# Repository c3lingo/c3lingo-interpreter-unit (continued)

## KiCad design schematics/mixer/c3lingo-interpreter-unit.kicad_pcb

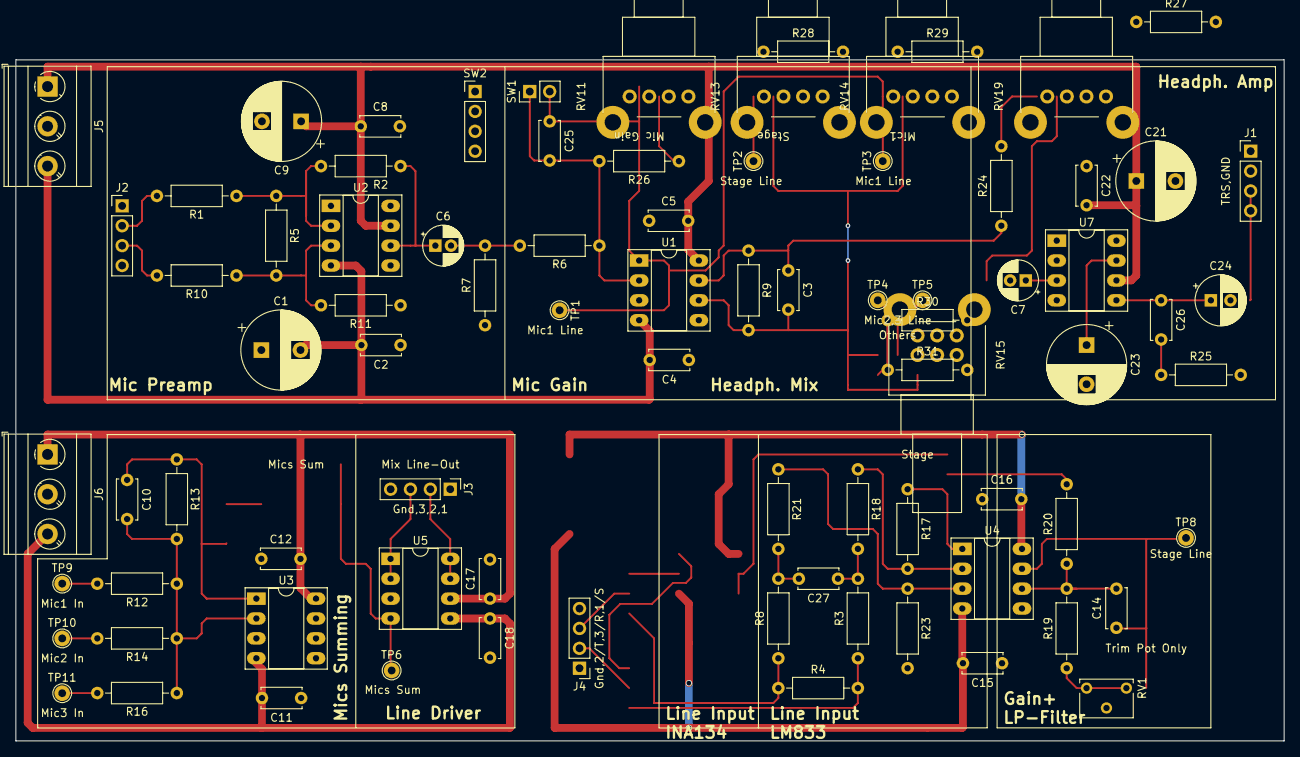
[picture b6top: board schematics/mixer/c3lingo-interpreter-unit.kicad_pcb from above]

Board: 2 copper layers, 162.0 x 87.0 mm, 83 parts (0 on the bottom side), 43 nets.

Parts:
C1, C9, C21, C23: 100uF; CP_Radial_D10.0mm_P5.00mm
C2, C4, C5, C8, C11, C12, C15, C16, C22, C25: 100nF; C_Disc_D5.0mm_W2.5mm_P5.00mm
C3, C10: 22pF; C_Disc_D5.0mm_W2.5mm_P5.00mm
C6, C7: 1uF; CP_Radial_D5.0mm_P2.00mm
C14: 47pF; C_Disc_D5.0mm_W2.5mm_P5.00mm
C17, C18: 1uF; C_Disc_D5.0mm_W2.5mm_P5.00mm
C24: 220uF; CP_Radial_D6.3mm_P2.50mm
C26: 47nF; C_Disc_D5.0mm_W2.5mm_P5.00mm
C27: 220pF; C_Disc_D5.0mm_W2.5mm_P5.00mm
J1: Headphone 1; PinHeader_1x04_P2.54mm_Vertical
J2: Mic 1; PinHeader_1x04_P2.54mm_Vertical
J3: Mix Line-Out; PinHeader_1x04_P2.54mm_Vertical
J4: Stage Line-In; PinHeader_1x04_P2.54mm_Vertical
J5, J6: PowerSupply; TerminalBlock_MetzConnect_Type073_RT02603HBLU_1x03_P5.08mm_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
R1, R10: 1K 1%; R_Axial_DIN0207_L6.3mm_D2.5mm_P10.16mm_Horizontal
R2, R11: 330K 1%; R_Axial_DIN0207_L6.3mm_D2.5mm_P10.16mm_Horizontal
R3, R8, R17, R18, R21, R23: 10K; R_Axial_DIN0207_L6.3mm_D2.5mm_P10.16mm_Horizontal
R4: 3.3K; R_Axial_DIN0207_L6.3mm_D2.5mm_P10.16mm_Horizontal
R5: 27K 1%; R_Axial_DIN0207_L6.3mm_D2.5mm_P10.16mm_Horizontal
R6: 1.5K; R_Axial_DIN0207_L6.3mm_D2.5mm_P10.16mm_Horizontal
R7: 470R; R_Axial_DIN0207_L6.3mm_D2.5mm_P10.16mm_Horizontal
R9, R12, R13, R14, R16, R19, R28, R29, R30, R31: 22K; R_Axial_DIN0207_L6.3mm_D2.5mm_P10.16mm_Horizontal
R20: 47K; R_Axial_DIN0207_L6.3mm_D2.5mm_P10.16mm_Horizontal
R24: 330K; R_Axial_DIN0207_L6.3mm_D2.5mm_P10.16mm_Horizontal
R25: 12R; R_Axial_DIN0207_L6.3mm_D2.5mm_P10.16mm_Horizontal
R26: 270R; R_Axial_DIN0207_L6.3mm_D2.5mm_P10.16mm_Horizontal
R27: 2.2K; R_Axial_DIN0207_L6.3mm_D2.5mm_P10.16mm_Horizontal
RV1: 100K; Potentiometer_Vishay_T73XX_Horizontal
RV11, RV13, RV14, RV19: 50K log.; Potentiometer_Alps_RK11K_Single_Horizontal
RV15: 50K log. st.; Potentiometer_Alps_RK09L_Double_Horizontal
SW1: Mute_1; PinHeader_1x02_P2.54mm_Vertical
SW2: OnAir_1; PinHeader_1x04_P2.54mm_Vertical
TP1, TP3, TP9: Mic1; TestPoint_THTPad_D2.0mm_Drill1.0mm
TP2, TP8: Stage; TestPoint_THTPad_D2.0mm_Drill1.0mm
TP4, TP10: Mic2; TestPoint_THTPad_D2.0mm_Drill1.0mm
TP5, TP11: Mic3; TestPoint_THTPad_D2.0mm_Drill1.0mm
TP6: MicSum; TestPoint_THTPad_D2.0mm_Drill1.0mm
U1, U3, U4: LM833N; DIP-8_W7.62mm_Socket_LongPads
U2: NE5534; DIP-8_W7.62mm_Socket_LongPads
U5: DRV134PA; DIP-8_W7.62mm_Socket_LongPads
U7: LM386N-4; DIP-8_W7.62mm_Socket_LongPads

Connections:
+15V: C5.2, C8.1, C9.1, C12.2, C16.2, C17.1, C21.1, C22.2, J5.1, J6.1, U1.8, U2.7, U3.8, U4.8, U5.6, U7.6
-15V: C1.2, C2.2, C4.2, C11.2, C15.2, C18.1, J5.3, J6.3, U1.4, U2.4, U3.4, U4.4, U5.5
GNDREF: C1.1, C2.1, C4.1, C5.1, C8.2, C9.2, C11.1, C12.1, C15.1, C16.1, C17.2, C18.2, C21.2, C22.1, C23.2, J2.1, J3.1, J4.1, J5.2, J6.2, R7.1, R11.1, R23.2, R25.2, R27.2, RV13.1, RV14.1, RV15.1, RV15.4, U1.3, U1.5, U3.3, U4.5, U5.3, U7.2, U7.4
Mic1: C25.1, R12.2, RV11.2, RV14.3, SW1.2, TP1.1, TP3.1, TP9.1, U1.1
unnamed: C3.1, R9.1, R24.1, U1.7
unnamed: C3.2, R9.2, R28.1, R29.1, R30.1, R31.1, U1.6
unnamed: C6.1, R2.1, U2.6
unnamed: C6.2, R6.2, R7.2
unnamed: C7.1, RV19.2
unnamed: C7.2, U7.3
unnamed: C10.1, R13.1, TP6.1, U3.1, U5.4
unnamed: C10.2, R12.1, R13.2, R14.1, R16.1, U3.2
unnamed: C14.2, R19.2, R20.1, U4.6
unnamed: C23.1, U7.7
unnamed: C24.1, C26.1, U7.5
unnamed: C25.2, R6.1, R26.2, SW1.1, U1.2
unnamed: C26.2, R25.1
unnamed: C27.1, R3.2, R18.2
unnamed: C27.2, R8.2, R21.2
unnamed: J2.2, R1.2
unnamed: J2.3, R10.2
unnamed: J3.2, U5.7, U5.8
unnamed: J3.3, U5.1, U5.2
unnamed: J4.2, R3.1, R4.2
unnamed: J4.3, R4.1, R8.1
unnamed: R1.1, R2.2, R5.1, U2.2
unnamed: R5.2, R10.1, R11.2, U2.3
unnamed: R14.2, TP10.1
unnamed: R16.2, TP11.1
unnamed: R17.1, R20.2, U4.1
unnamed: R17.2, R18.1, U4.2
unnamed: R19.1, RV1.1
unnamed: R21.1, R23.1, U4.3
unnamed: R24.2, RV19.3
unnamed: R26.1, RV11.1
unnamed: R27.1, RV19.1
unnamed: R28.2, RV13.2
unnamed: R29.2, RV14.2
unnamed: R30.2, RV15.5
unnamed: R31.2, RV15.2
unnamed: RV15.3, TP5.1
unnamed: RV15.6, TP4.1
Stage: C14.1, RV1.2, RV13.3, TP2.1, TP8.1, U4.7

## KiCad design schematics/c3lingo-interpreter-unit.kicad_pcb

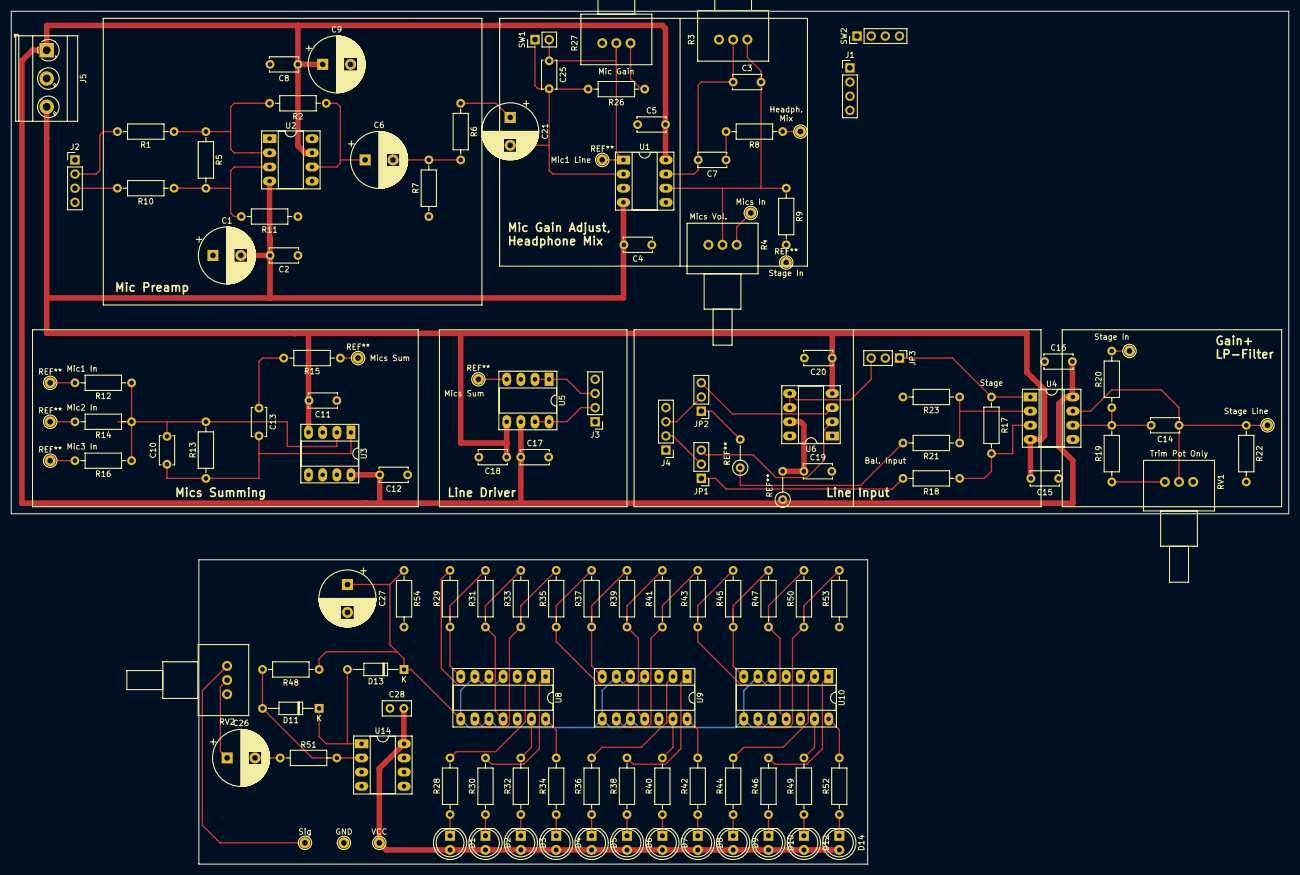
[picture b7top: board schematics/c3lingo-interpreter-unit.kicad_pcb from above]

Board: 2 copper layers, 229.2 x 153.0 mm, 117 parts (0 on the bottom side), 77 nets.

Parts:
C1, C9: 100uF; CP_Radial_D10.0mm_P5.00mm
C2, C4, C5, C8, C11, C12, C15, C16: 100nF; C_Disc_D5.0mm_W2.5mm_P5.00mm
C3, C10: 22pF; C_Disc_D5.0mm_W2.5mm_P5.00mm
C6, C21: 10uF; CP_Radial_D10.0mm_P5.00mm
C7: 10nF; C_Disc_D5.0mm_W2.5mm_P5.00mm
C13: 4.7pF; C_Disc_D5.0mm_W2.5mm_P5.00mm
C14: 47pF; C_Disc_D5.0mm_W2.5mm_P5.00mm
C17, C18, C19, C20: 1uF; C_Disc_D5.0mm_W2.5mm_P5.00mm
C25: 0.1uF; C_Disc_D5.0mm_W2.5mm_P5.00mm
C26: TODO; CP_Radial_D10.0mm_P5.00mm
C27: 2.2uF; CP_Radial_D10.0mm_P5.00mm
C28: 100nF; C_Disc_D5.0mm_W2.5mm_P2.50mm
D1, D9, D10, D12, D14: LED rd; LED_D5.0mm
D2, D3, D7, D8: LED ye; LED_D5.0mm
D4, D5, D6: LED gn; LED_D5.0mm
D11, D13: 1N4148; D_DO-35_SOD27_P10.16mm_Horizontal
GND: TestPoint_THTPad_D2.0mm_Drill1.0mm
J1: Headphone 1; PinHeader_1x04_P2.54mm_Vertical
J2: Mic 1; PinHeader_1x04_P2.54mm_Vertical
J3: Mix Line-Out; PinHeader_1x04_P2.54mm_Vertical
J4: Stage Line-In; PinHeader_1x04_P2.54mm_Vertical
J5: PowerSupply; TerminalBlock_MetzConnect_Type073_RT02603HBLU_1x03_P5.08mm_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
JP1: Stage Hot; PinHeader_1x03_P2.54mm_Vertical
JP2: Stage Cold; PinHeader_1x03_P2.54mm_Vertical
JP3: Stage Out; PinHeader_1x03_P2.54mm_Vertical
Mics In: TestPoint_THTPad_D2.0mm_Drill1.0mm
R1, R10: 1K 1%; R_Axial_DIN0207_L6.3mm_D2.5mm_P10.16mm_Horizontal
R2, R11: 330K 1%; R_Axial_DIN0207_L6.3mm_D2.5mm_P10.16mm_Horizontal
R3, R4: 22K; Potentiometer_Vishay_148-149_Single_Horizontal
R5: 27K 1%; R_Axial_DIN0207_L6.3mm_D2.5mm_P10.16mm_Horizontal
R6, R26: 120R; R_Axial_DIN0207_L6.3mm_D2.5mm_P10.16mm_Horizontal
R7: 5.6K; R_Axial_DIN0207_L6.3mm_D2.5mm_P10.16mm_Horizontal
R8, R15: 47R; R_Axial_DIN0207_L6.3mm_D2.5mm_P10.16mm_Horizontal
R9, R12, R13, R14, R16, R19, R22: 22K; R_Axial_DIN0207_L6.3mm_D2.5mm_P10.16mm_Horizontal
R17, R18, R21, R23, R28, R29, R30, R31, R32, R33, R34, R35, R36, R37, R38, R39, R40, R41, R42, R43, R44, R45, R46, R47, R49, R50, R52: R; R_Axial_DIN0207_L6.3mm_D2.5mm_P10.16mm_Horizontal
R20: 47K; R_Axial_DIN0207_L6.3mm_D2.5mm_P10.16mm_Horizontal
R27: 25K; Potentiometer_Vishay_148-149_Single_Horizontal
R48: 100K; R_Axial_DIN0207_L6.3mm_D2.5mm_P10.16mm_Horizontal
R51: 25K; R_Axial_DIN0207_L6.3mm_D2.5mm_P10.16mm_Horizontal
R53: 1K; R_Axial_DIN0207_L6.3mm_D2.5mm_P10.16mm_Horizontal
R54: 10K; R_Axial_DIN0207_L6.3mm_D2.5mm_P10.16mm_Horizontal
RV1: 100K; Potentiometer_Vishay_148-149_Single_Horizontal
RV2: 50K; Potentiometer_Vishay_148-149_Single_Horizontal
SW1: Mute_1; PinHeader_1x02_P2.54mm_Vertical
SW2: OnAir_1; PinHeader_1x04_P2.54mm_Vertical
Sig: TestPoint_THTPad_D2.0mm_Drill1.0mm
U1, U3, U4, U14: LM833N; DIP-8_W7.62mm_Socket_LongPads
U2: NE5534; DIP-8_W7.62mm_Socket_LongPads
U5: DRV134PA; DIP-8_W7.62mm_Socket_LongPads
U6: INA134PA; DIP-8_W7.62mm_Socket_LongPads
U8, U9, U10: LM339; DIP-14_W7.62mm_Socket_LongPads
VCC: TestPoint_THTPad_D2.0mm_Drill1.0mm

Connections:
+15V: C5.2, C8.1, C9.1, C12.2, C16.2, C17.1, C19.1, C28.2, D1.2, D2.2, D3.2, D4.2, D5.2, D6.2, D7.2, D8.2, D9.2, D10.2, D12.2, D14.2, J5.1, U1.8, U2.7, U3.8, U4.8, U5.6, U6.7, U8.3, U9.3, U10.3, U14.8, VCC.1
-15V: C1.2, C2.2, C4.2, C11.2, C15.2, C18.1, C20.1, J5.3, U1.4, U2.4, U3.4, U4.4, U5.5, U6.4
GNDREF: C1.1, C2.1, C4.1, C5.1, C8.2, C9.2, C11.1, C12.1, C15.1, C16.1, C17.2, C18.2, C19.2, C20.2, C27.2, C28.1, GND.1, J2.1, J3.1, J4.1, J5.2, R4.1, R7.1, R11.1, R22.2, R23.2, R53.1, R54.2, RV2.3, U1.3, U1.5, U3.3, U4.5, U5.3, U6.1, U8.12, U9.12, U10.12, U14.3, U14.4
Mic1: C25.1, R12.2, R27.2, RV2.1, SW1.2, Sig.1, U1.1
MicSum: Mics In.1, R4.3, R15.1, U5.4
unnamed: C3.1, C7.2, R3.2, U1.7
unnamed: C3.2, R3.1, R4.2, R9.1, U1.6
unnamed: C6.1, R2.1, U2.6
unnamed: C6.2, R6.2, R7.2
unnamed: C7.1, R8.2
unnamed: C10.1, C13.2, R13.1, U3.1
unnamed: C10.2, R12.1, R13.2, R14.1, R16.1, U3.2
unnamed: C13.1, R15.2
unnamed: C14.2, R19.2, R20.1, U4.6
unnamed: C21.1, R6.1
unnamed: C21.2, C25.2, R26.2, SW1.1, U1.2
unnamed: C26.1, RV2.2
unnamed: C26.2, R51.1
unnamed: C27.1, D13.1, R48.1, R54.1, U8.4, U8.6, U8.8, U8.10, U9.4, U9.6, U9.8, U9.10, U10.4, U10.6, U10.8, U10.10
unnamed: D1.1, R28.1
unnamed: D2.1, R30.1
unnamed: D3.1, R32.1
unnamed: D4.1, R34.1
unnamed: D5.1, R36.1
unnamed: D6.1, R38.1
unnamed: D7.1, R40.1
unnamed: D8.1, R42.1
unnamed: D9.1, R44.1
unnamed: D10.1, R46.1
unnamed: D11.1, D13.2, U14.1
unnamed: D11.2, R48.2, R51.2, U14.2
unnamed: D12.1, R49.1
unnamed: D14.1, R52.1
unnamed: J2.2, R1.2
unnamed: J2.3, R10.2
unnamed: J3.2, U5.7, U5.8
unnamed: J3.3, U5.1, U5.2
unnamed: J4.2, JP1.2
unnamed: J4.3, JP2.2
unnamed: JP1.1, R18.2
unnamed: JP1.3, U6.2
unnamed: JP2.1, R21.2
unnamed: JP2.3, U6.3
unnamed: JP3.1, R17.1, U4.1
unnamed: JP3.2, R20.2
unnamed: JP3.3, U6.5, U6.6
unnamed: R1.1, R2.2, R5.1, U2.2
unnamed: R5.2, R10.1, R11.2, U2.3
unnamed: R17.2, R18.1, U4.3
unnamed: R19.1, RV1.1
unnamed: R21.1, R23.1, U4.2
unnamed: R26.1, R27.1
unnamed: R28.2, U8.2
unnamed: R29.1, R31.2, U8.7
unnamed: R29.2, U8.5
unnamed: R30.2, U8.1
unnamed: R31.1, R33.2, U8.11
unnamed: R32.2, U8.13
unnamed: R33.1, R35.2, U8.9
unnamed: R34.2, U8.14
unnamed: R35.1, R37.2, U9.5
unnamed: R36.2, U9.2
unnamed: R37.1, R39.2, U9.7
unnamed: R38.2, U9.1
unnamed: R39.1, R41.2, U9.11
unnamed: R40.2, U9.13
unnamed: R41.1, R43.2, U9.9
unnamed: R42.2, U9.14
unnamed: R43.1, R45.2, U10.5
unnamed: R44.2, U10.2
unnamed: R45.1, R47.2, U10.7
unnamed: R46.2, U10.1
unnamed: R47.1, R50.2, U10.11
unnamed: R49.2, U10.13
unnamed: R50.1, R53.2, U10.9
unnamed: R52.2, U10.14
Stage: C14.1, R9.2, R22.1, RV1.2, U4.7

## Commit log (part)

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2020-10-04 [DOC] Add basic requirements
2020-10-12 Schematic: Proof of concept (one microphone)
2020-11-01 Docs: Add signal flow graph
2020-11-02 Schematic: Bugfixes, VU meter draft, first development PCB draft
2020-11-09 Move VU-Meter to own project
2020-11-09 Schematic Main: Add corrected headphone amp
2020-11-10 update schematic PDFs
2020-11-12 Refine headphone mix requirements, fix signal flow
2020-11-12 final fixes for first prototype PCB order
2020-12-13 VU meter: add -15V, fix footprints, specify LED resistors
    TODO: Decide on signal smoothing
2020-12-13 Main: Summing design flaw fixed; better headphone vol. range
    - Multiple R and C value adaptions
    - Line Input: No relevant difference between INA134 and own circuit -> LM833 chosen
    - Signal busses/ summing module inputs fixed
    - TODO: On-Air Button
    - TODO: Update PCB layout
2020-12-13 Main: Add 15V phantom power
2021-02-07 Add UI layout draft
2021-02-15 Decide on a potentiometer for UI elements (schematic outdated!)
2021-04-11 [TIDY] restructure readme
2021-04-11 [DOC] reworked potentiometer options
2021-04-17 [DOC] reworked button/ switch options
2021-05-22 [DOC] Add some data sheets
2021-05-23 [TIDY] Split old design in new hierarchal layout
    TODO: Shrink channel strip to A4 paper size, integrate VU meter
2021-05-23 [TIDY] Channel Strip: Integrate VU Meter
2021-05-30 Schematics: Add missing functionality, add footprints, fix todos
    - Add On-Air button
    - Lower frequency for the input HPF
    - (final) button footprints
    - (final) potentiometer values and footprints
2021-06-02 PCB: Line in/out and mics summing design
2021-06-02 PCB: Channel strip design
2021-06-03 [DOC] Add BOM with some approx. prices
2021-09-02 [TIDY] remove old VU meter project
2021-09-05 [FIX] Schematics: Revised values and PCB errata text
    * fixed trim pot range at VU meter
    * TODOs removed (5V V_LED didn't work out, 10uF at LM386 wasn't better, VU meter filtering not needed)
    * phantom power voltage changed and readme chapter added
    * hardware errata: gain pot. pins are swapped, ground plane isn't fully connected
    Footprints and PCB aren't fixed to keep the schematic compatible with the existing PCBs!
2022-12-04 Upgrade project to KiCad 6
    Item annotations were re-generated as there were duplicate items otherwise somehow. This means, that some item numbers have changed!
2022-12-30 KiCad 6: Update power flag symbols
    Power flags were updated in the new KiCad 6 library, which was a warning in the ERC.
2023-01-04 Fix 3D model paths for KiCad 6
2023-01-04 Schematics: Fix multiple issues with initial prototype
    - Removed high-pass filter between microphone pre-amp and gain as it made things sound worse
    - Removed low-pass filter before VU meter as it looked fine without
    - Connect VU meter to +15 V directly as 5 V didn't work
    - Footprint of the gain potentiometer (Alps RK09) seems to be fixed with the KiCad 6 library
2023-01-04 PCB: Update for new schematic (still THT for now)
2023-01-04 Update footprints to KiCad 6
2023-01-05 Readme: Notes on (unsuitable) housing options
2023-01-15 [TIDY] Split channel into two schematics
2024-02-23 Update to KiCad 7
2024-03-04 new headphone amp IC (board layout not updated)
2024-06-30 Update to KiCad 8
2024-06-30 Reworks board-to-board connections
    Instead of having connections between all boards, use the mix_io board as an audio signal distribution hub.
    Note: PCB not updated
2024-07-06 Re-layout boards with SMD components
    * Channel Mix: Removed vu meter potentiometer as good setting was found (10 dB
    more headroom)
    * Channel Mix: Add vu meter alternate power
    * Channel I/O: Added jumper for phantom power enable/disable
    * Add GND test points
2024-07-07 Fix date on PCB dimensions PDF
2024-07-07 Channel-Mix: Rework LED supply voltage
2024-07-11 chore: Split readme
2024-07-11 Mix I/O: Add ground lift
2024-07-11 Channel I/O: Fix headphone amp caps, re-phrase readme section
2024-07-11 Channel Mixer: Fix LP filter at mic gain
    1nF has about 15kHz cutoff frequency at full gain
2024-08-18 Tidy: Rename hierarchical labels
2024-08-18 Channel Mixer: Add LP filter to V/U meter
    Note: schematic and dimenstions PDFs not updated as more changes come
    To reduce HF noise on the power rail introduced by the switching of the comperators
2024-09-06 Channel Mixer: Rework muting mechanism
    Note: Schematic PDF not updated yet
2024-09-06 Channel: Change to single channel potentiometers
2024-09-08 Move potentiometers down, fix JLC PCB components
    - Fix JLC PCB component orientation
    - Add do-not-populate to all THD components
    - Fix JLC part selection, tweak values to be standard components
2024-09-08 [TIDY] Readme: Move BOM to separate file
2024-09-12 TMP: What to order
2024-09-16 [TIDY] set position origin to PCB edge
2024-10-01 WIP: New values
    TODO: JLC component ID, update PCB
2024-11-21 Add rework to fix VU meter, muting delay, LP filters
    Note: PCB files were not upated!
    Changes/ required manual rework:
    - Replace C314 with 100nF to reduce muting fade time
    - Replace C301 with 680pF to have a 12 kHz low-pass filter on headphones
    - Replace R309, R232, R335 to fix VU meter range (steps are a bit wonky
    afterwards, but top (and bottom) range are a lot more save now)
2024-11-28 Add 3D models for connectors and potis
    Used Alps RK09L1140 instead of CUI PTN09X as I haven't found a model for the actual part and the other one has the same dimensions.
    Also the axle in the model for the Alps RK09K is probably too long.
2024-12-03 Button cap for the channel mute switch
2024-12-18 WIP Channel Mixer: Reduce mic and output gain
    Note: Schematics not re-exported!
    TODO: Do we need to adjust C313 too? What is is for anyways?
2024-12-18 Channel Mixer: Re-design VU meter scale
    Note: Schematic not re-exported!
2024-12-18 Line I/O: Remove gain adjustment (PCB not updated!)
    Tweaking the line input gain is not necessary as the users will adjust the volume to personal preference anyways.
    Note: PCB not updated!
2025-08-26 chore: Tweak .gitignore
2025-08-26 Update to KiCad 9
2025-08-26 Line I/O: Optimize Schematic and update PCB
    Share one LM833 instead of only using one half for summing and line input each.
2025-08-26 Channel Mixer: Reduce mic and output gain
    Note: Schematics not re-exported!
2025-08-26 Change inter-PCB connections to IDC connectors
2025-08-26 Refactor: Rename component rotation
    The latest release of the (JLC PCB) Fabrication Toolkit plugin needs the rotation offset field to be named "FT Rotation Offset"
2025-08-26 Channel-Mixer: Change VU meter LEDs footprint to 5x2mm THD
2025-08-26 Channel I/O: Mark phantom power testpoint as DNP
    It's just a footprint to solder a wire on and no component to populate.
2025-08-30 Channel I/O: Fix value of C601
2025-08-30 docs/bom: Add note about housing and power supply
2025-09-08 Line I/O: Fix polarity of C210
2025-09-08 Channel-Mixer: Fix silkscreen label of TP305
2025-09-19 Channel-Mixer: Replace mute-button connector
2025-09-19 docs/bom: Add C14 power socket
2025-09-19 Channel-Mixer: Change mute LED to 3mm THD
2025-09-19 WIP: Add some artwork to the PCBs
    TODO: OSHW
2025-09-22 Add git ignores for FreeCAD
2025-09-22 PCBs: Fix 3D models, add model for on/off switch
2025-09-23 Add 3rd Party License / Disclaimer
2025-09-23 Add 3rd Party Data License / Disclaimer
2025-09-23 clean up unused files
2025-09-23 Initial Commit of Custom Housing
2025-09-23 Channel-Mixer: Fix position of gain potentiometer
2025-09-23 docs/bom: Change mute button
2025-09-23 Fix position of gain potentiometer in Housing
2025-09-28 Channel-Mixer: Invert mute LED logic (to be an on-air LED)
2025-09-28 Channel-Mixer: Add buffer cap for VU meter LEDs
2025-09-29 Channel: Swap mic and headphone signal on IDC connector
2025-09-29 Channel-IO: Use horizontal IDC connector
2025-09-29 project settings: Fix 3D viewports
2025-10-07 Channel I/O: Change to 90° Connector Update FreeCAD license info to CC-BY-SA-4.0
2025-10-14 Ergonomics: extend housing width to 354mm
2025-10-15 add powersupply and ac connector to assembly
2025-10-16 Add some artwork to the PCBs
2025-10-16 chore: Bump version number, plot schematic
2025-10-16 chore: Remove old 3D models
2025-10-16 Housing: Initial version of custom housing
2025-10-22 Add PE connection points and improved ventilation
2025-10-27 add PE Studs and Tech Drawings
2025-10-27 fix typo
2025-10-29 bom: Switch 3mm LED spacer
2025-10-29 bom: select new poti knobs
    Re'an F311 is not available any more at all.
2025-10-29 Housing: Add PE connection points and improved ventilation
2025-10-29 channel: Select alternate JLCPCB parts
    Some capacitors were not in stock any more, so select some other ones
2025-10-29 Channel-Mixer: Fix on-air LED resistor
2025-10-29 PCBs: Add placeholder for serial 2D barcode
2025-11-03 Housing: Add hardware to BOM
2025-11-03 bom: Remove price column, reorder some rows
2025-11-03 FIXUP: Mouser arrived (minus 19 button caps)
2025-11-03 WIP: Add order list
2025-11-03 FIXUP: Ordered screws and alternate IDC cable
2025-11-07 FIXUP: Incoming parcels
2025-11-25 housing: small tweaks
2025-11-26 Mechanical: Add assembly helpers
2025-11-27 FIXUP: Mouser complete
2025-11-27 Docs: Update level meter colors in UI mockup
2025-11-27 FIXUP: New front plate layout
2025-11-27 WIP Housing: Add front plate print
2025-11-27 Housing: Add nameplate
